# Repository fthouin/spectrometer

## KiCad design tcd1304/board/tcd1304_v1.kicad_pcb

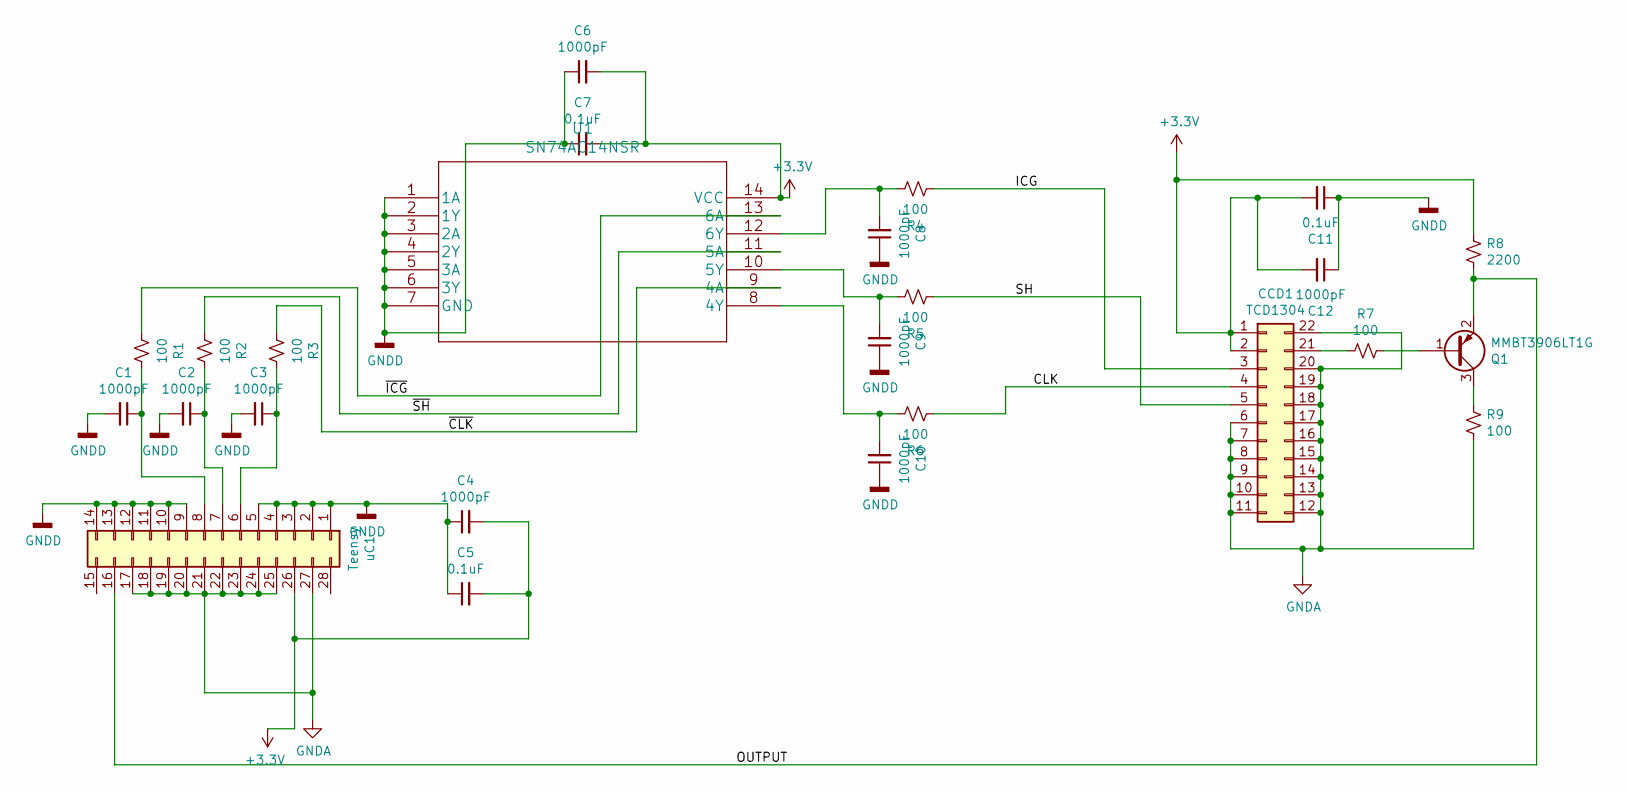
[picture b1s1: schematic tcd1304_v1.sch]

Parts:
C1, C2, C3, C4, C6, C8, C9, C10, C12: 1000pF; C_0603_1608Metric
C5, C7, C11: 0.1uF; C_0603_1608Metric
CCD1: TCD1304; DIP-22_W10.16mm_Socket_LongPads
Q1: MMBT3906LT1G; SOT-23
R1, R2, R3, R4, R5, R6, R7, R9: 100; R_0603_1608Metric
R8: 2200; R_0603_1608Metric
U1: SN74AC14NSR
uC1: Teensy; DIP-28_W15.24mm_Socket

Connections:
+3V3: C4.2, C5.2, C6.2, C7.2, C11.2, C12.2, CCD1.1, CCD1.2, R8.1, U1.14 (VCC), uC1.26
/CLK: CCD1.4, R6.2
/ICG: CCD1.3, R4.2
/OUTPUT: Q1.2 (E), R8.2, uC1.16
/SH: CCD1.5, R5.2
/~CLK: R3.2, U1.9 (4A)
/~ICG: R1.2, U1.13 (6A)
/~SH: R2.2, U1.11 (5A)
GNDA: CCD1.6, CCD1.7, CCD1.8, CCD1.9, CCD1.10, CCD1.11, CCD1.12, CCD1.13, CCD1.14, CCD1.15, CCD1.16, CCD1.17, CCD1.18, CCD1.19, CCD1.20, CCD1.22, R9.2, uC1.17, uC1.18, uC1.19, uC1.20, uC1.21, uC1.22, uC1.23, uC1.24, uC1.25, uC1.27
GNDD: C1.2, C2.2, C3.2, C4.1, C5.1, C6.1, C7.1, C8.1, C9.1, C10.1, C11.1, C12.1, U1.1 (1A), U1.2 (1Y), U1.3 (2A), U1.4 (2Y), U1.5 (3A), U1.6 (3Y), U1.7 (GND), uC1.1, uC1.2, uC1.3, uC1.4, uC1.5, uC1.9, uC1.10, uC1.11, uC1.12, uC1.13, uC1.14
unnamed: C1.1, R1.1, uC1.8
unnamed: C2.1, R2.1, uC1.7
unnamed: C3.1, R3.1, uC1.6
unnamed: C8.2, R4.1, U1.12 (6Y)
unnamed: C9.2, R5.1, U1.10 (5Y)
unnamed: C10.2, R6.1, U1.8 (4Y)
unnamed: CCD1.21, R7.2
unnamed: Q1.1 (B), R7.1
unnamed: Q1.3 (C), R9.1

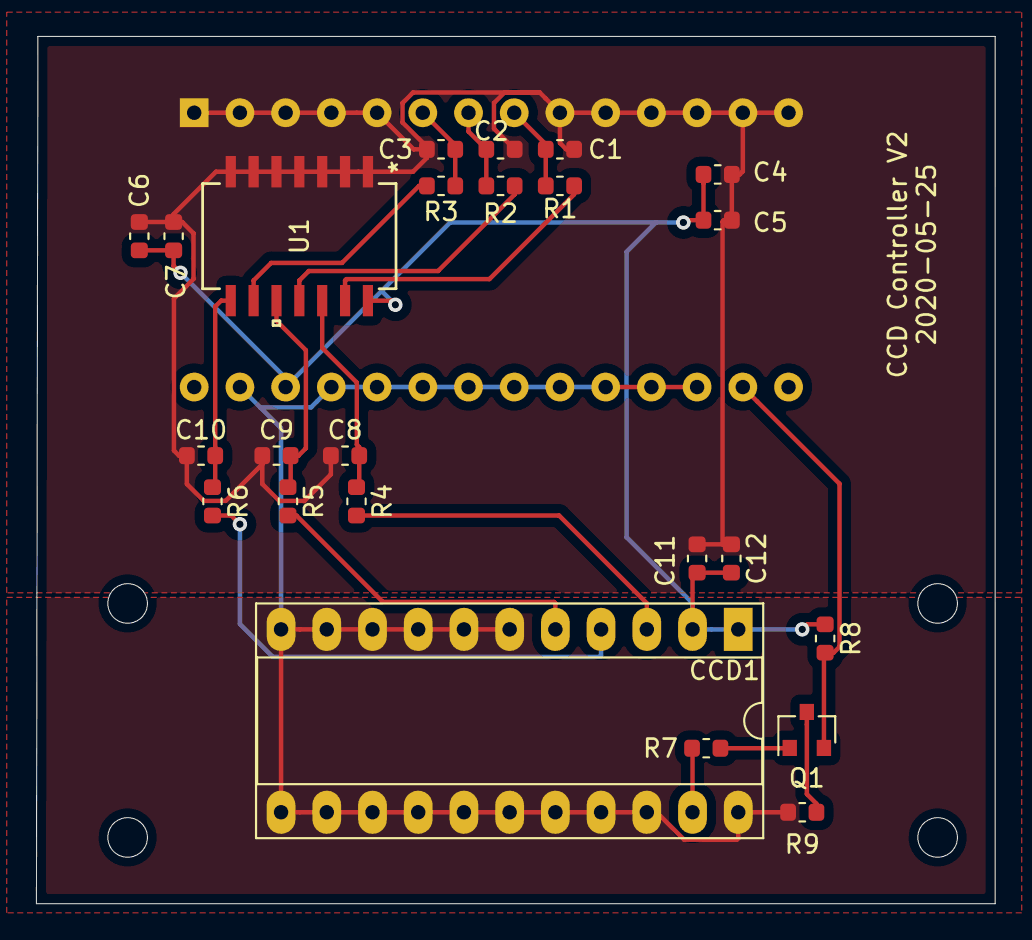
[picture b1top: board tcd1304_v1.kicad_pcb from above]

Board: 2 copper layers, 53.3 x 48.2 mm, 29 parts (1 on the bottom side), 19 nets.

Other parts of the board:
 : MountingHole_2.2mm_M2
 #2,  #3,  #4: MountingHole_2.2mm_M2

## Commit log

2020-03-23 Added the control firmware (might not work) and the first version of the PCB board!
2020-05-06 Added libraries for TCD1304 scheme and PCB
2020-05-26 New version for the PCB
2020-05-26 New version for the PCB (updated silk screen)

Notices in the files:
parts and their libraries:
Copyright 2016 Accelerated Designs. All rights reserved.
